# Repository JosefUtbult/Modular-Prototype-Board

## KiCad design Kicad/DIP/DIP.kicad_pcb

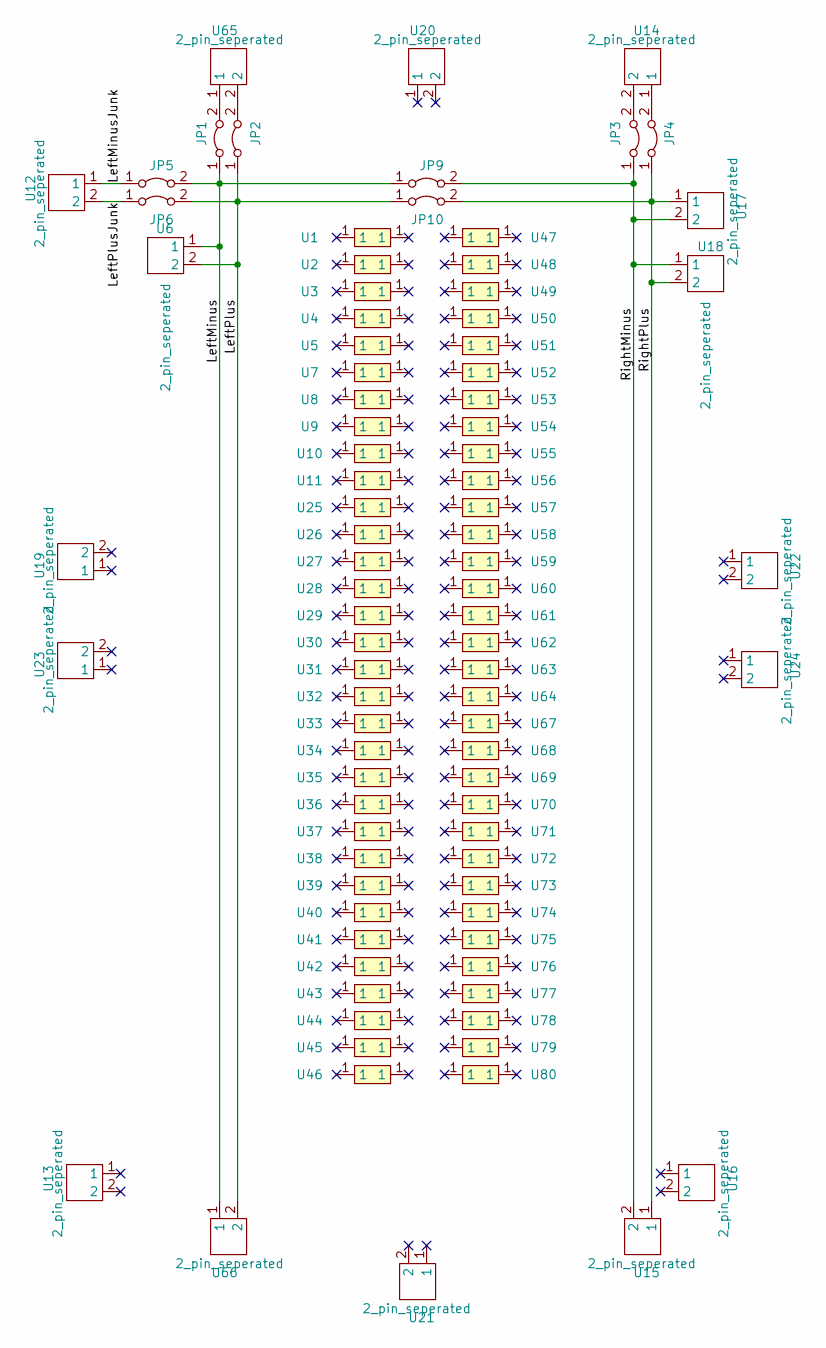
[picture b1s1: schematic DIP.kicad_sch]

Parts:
JP1, JP2, JP3, JP4, JP5, JP6, JP9, JP10: Jumper_2_Bridged; SolderJumper-2_P1.3mm_Bridged_RoundedPad1.0x1.5mm
U1, U2, U3, U47, U48: 1_row_connected; 8_pin_connection
U4, U5, U7, U8, U9, U10, U11, U25, U26, U27, U28, U29, U30, U31, U32, U33, U34, U35, U36, U37, U38, U39, U40, U41, U42, U43, U44, U45, U46, U49, U50, U51, U52, U53, U54, U55, U56, U57, U58, U59, U60, U61, U62, U63, U64, U67, U68, U69, U70, U71, U72, U73, U74, U75, U76, U77, U78, U79, U80: 1_row_connected; 9_pin_connection
U6: 2_pin_seperated; 30x2_pin_connected
U12, U13, U14, U15, U16, U17, U19, U20, U21, U22, U23, U24, U65, U66: 2_pin_seperated
U18: 2_pin_seperated; 31x2_pin_connected

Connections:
/LeftMinus: JP1.1 (A), JP5.2 (B), JP9.1 (A), U6.1, U66.1
/LeftMinusJunk: JP5.1 (A), U12.1
/LeftPlus: JP2.1 (A), JP6.2 (B), JP10.1 (A), U6.2, U66.2
/LeftPlusJunk: JP6.1 (A), U12.2
/RightMinus: JP3.1 (A), JP9.2 (B), U15.2, U17.2, U18.1
/RightPlus: JP4.1 (A), JP10.2 (B), U15.1, U17.1, U18.2
unnamed: JP1.2 (B), U65.1
unnamed: JP2.2 (B), U65.2
unnamed: JP3.2 (B), U14.2
unnamed: JP4.2 (B), U14.1

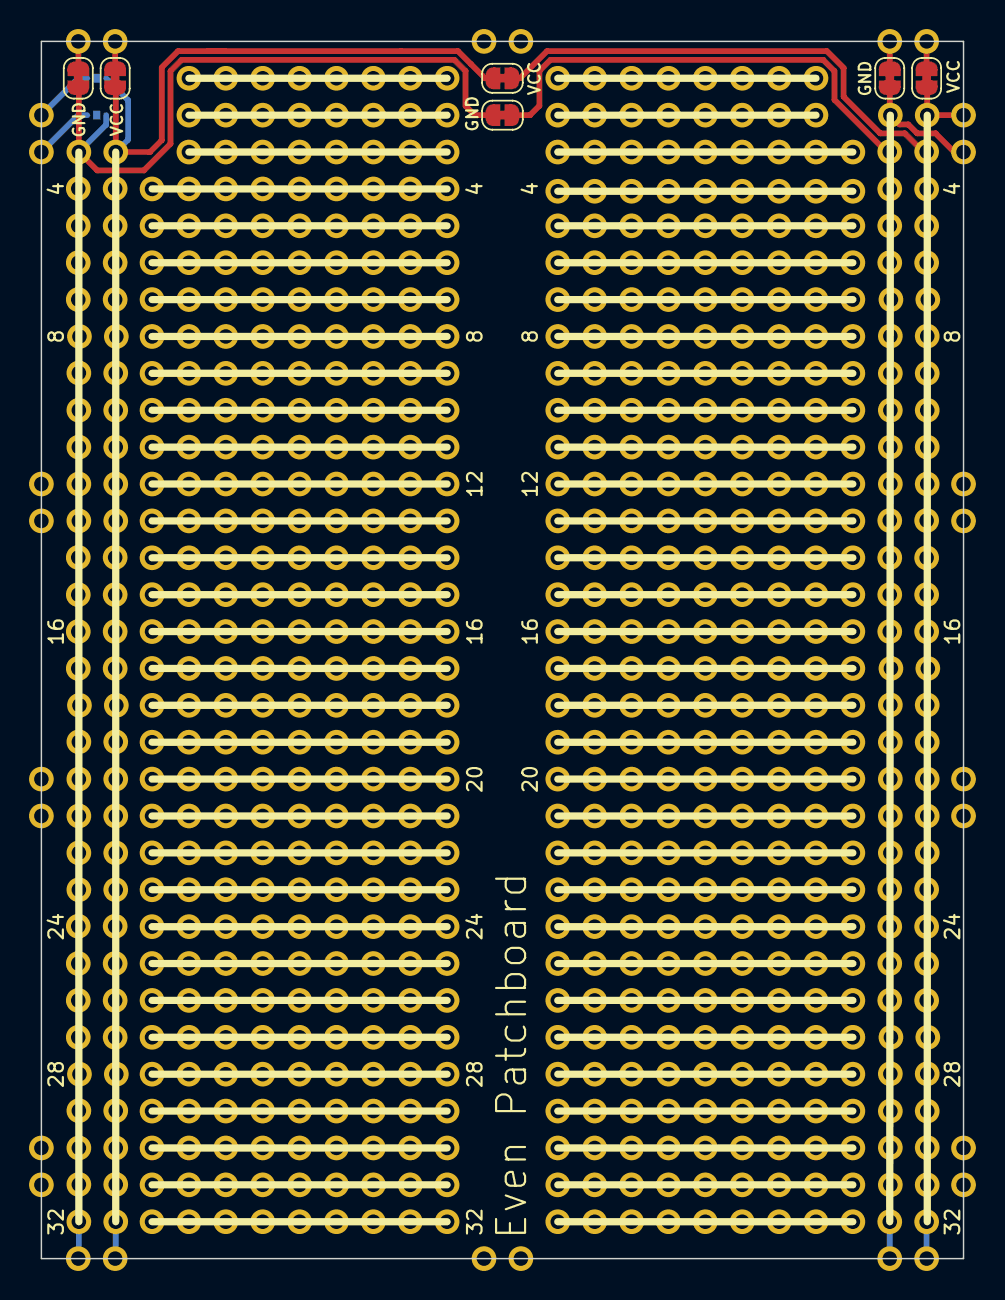
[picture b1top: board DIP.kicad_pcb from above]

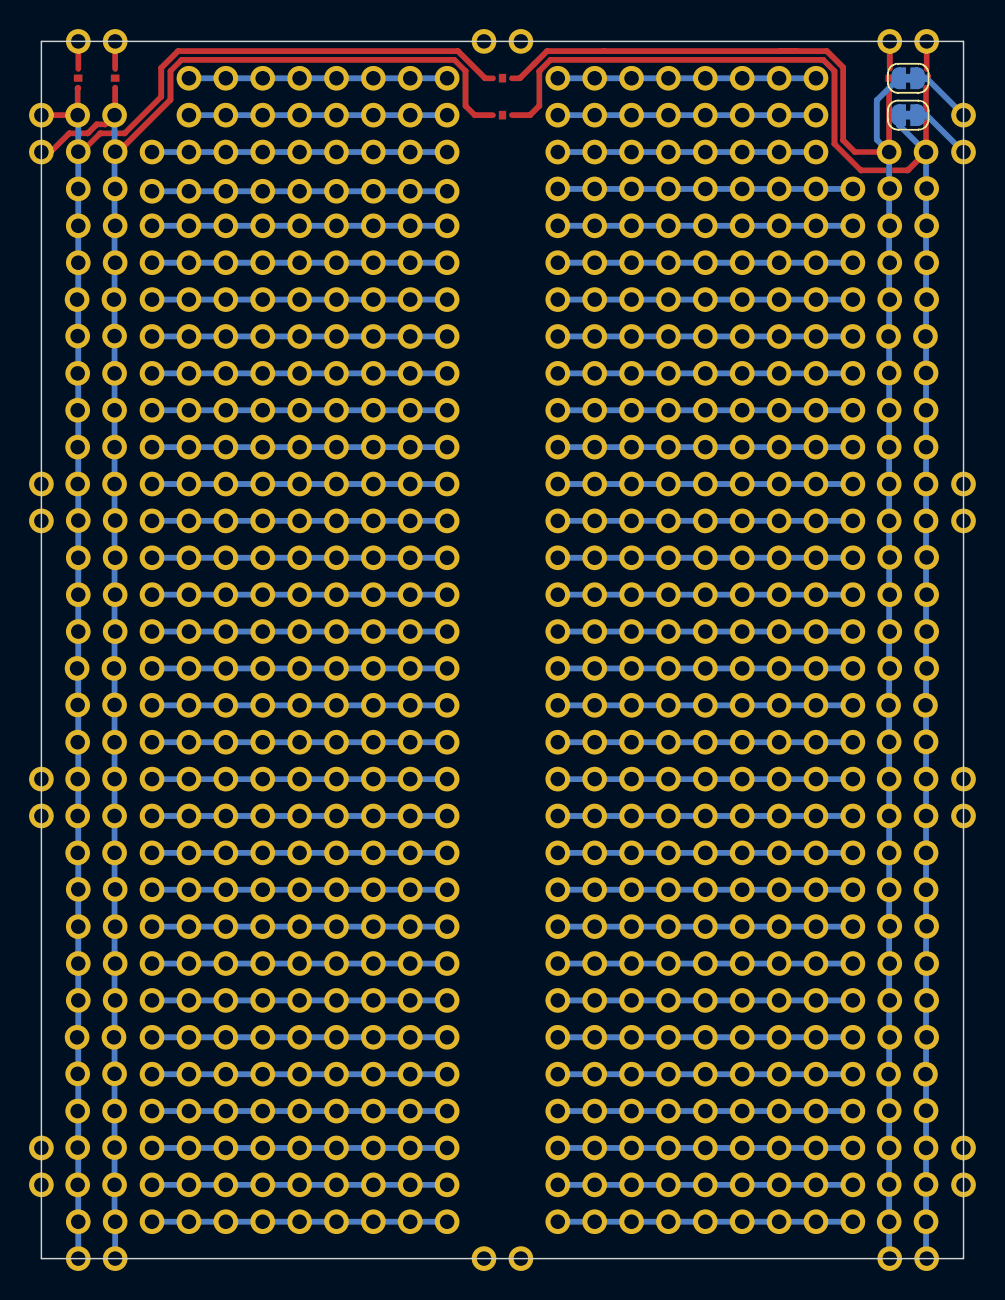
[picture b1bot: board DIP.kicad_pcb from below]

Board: 2 copper layers, 63.5 x 83.8 mm, 88 parts (2 on the bottom side), 10 nets.

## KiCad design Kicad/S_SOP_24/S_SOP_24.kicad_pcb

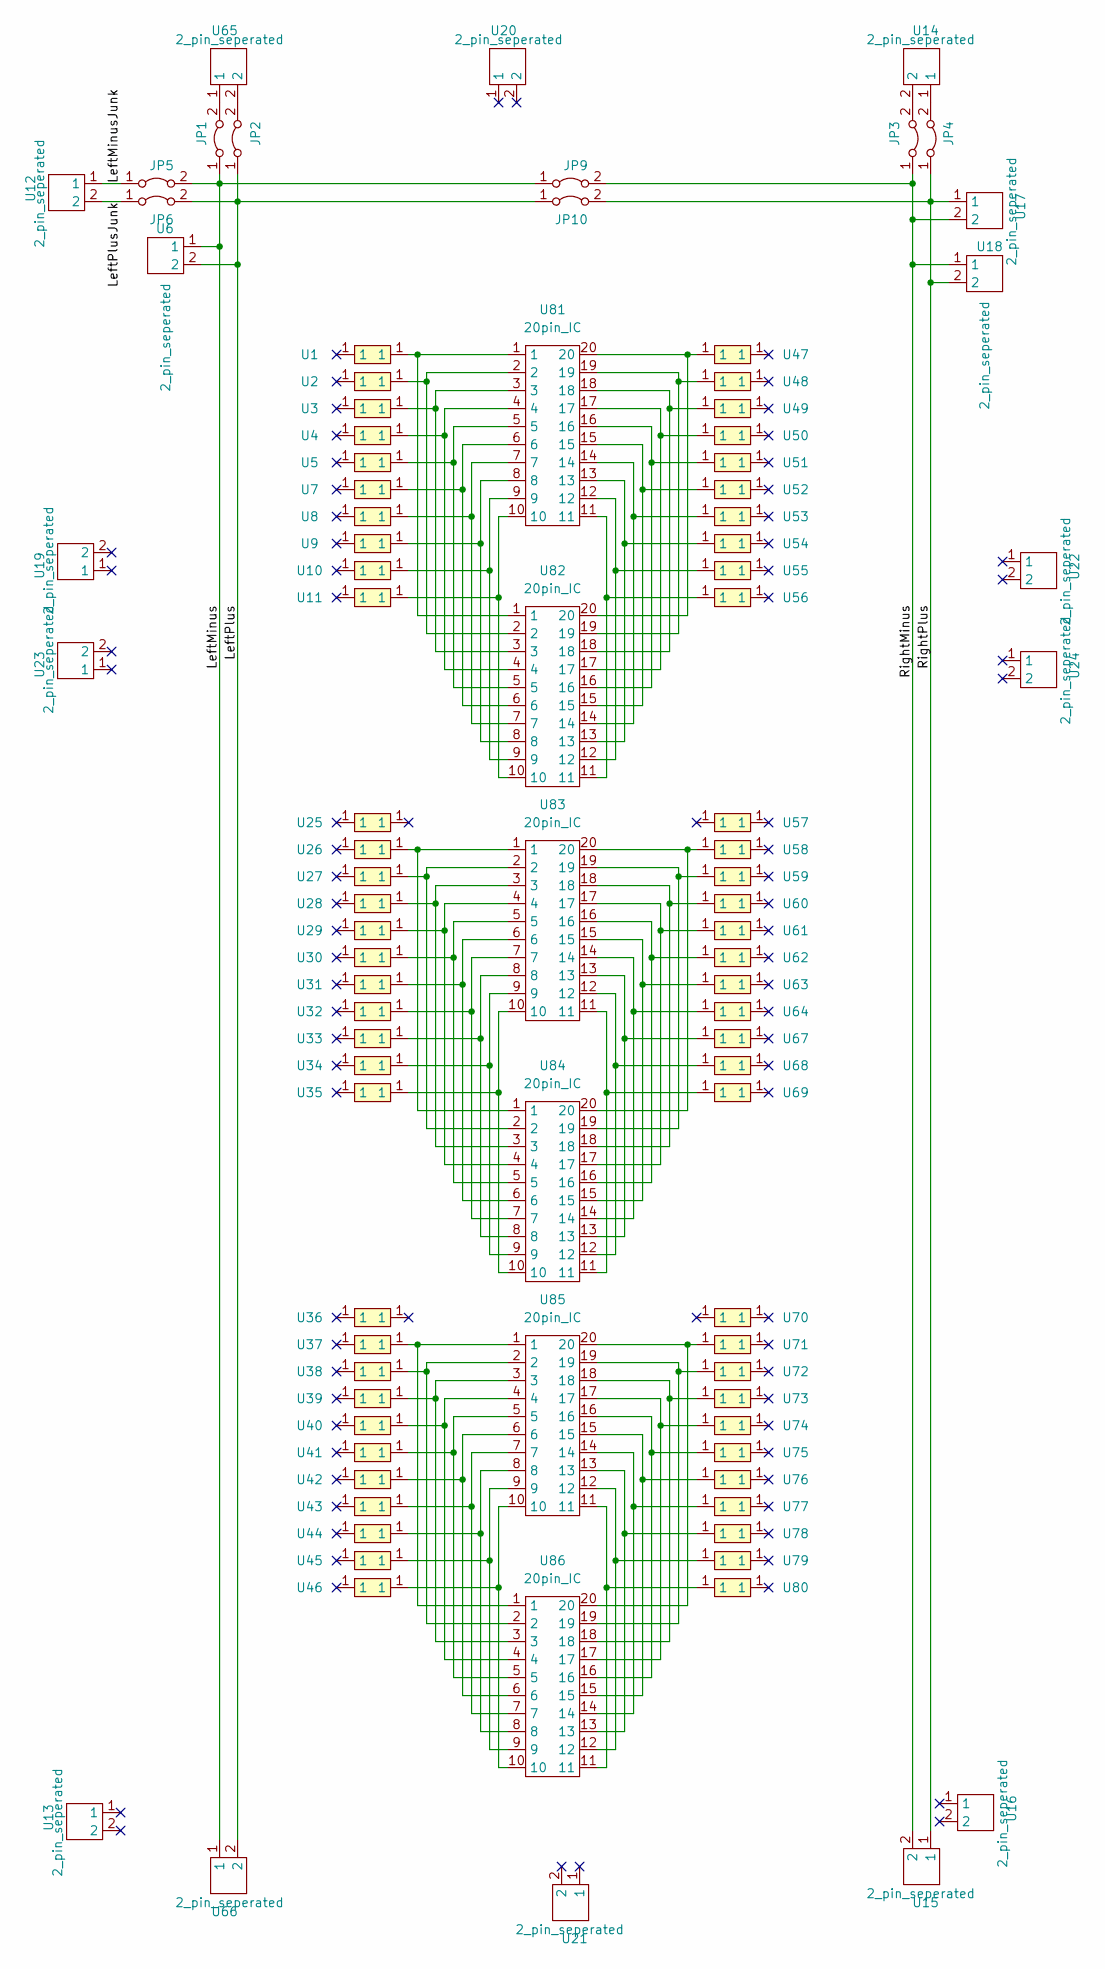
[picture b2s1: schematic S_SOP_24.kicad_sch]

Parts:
JP1, JP2, JP3, JP4, JP5, JP6, JP9, JP10: Jumper_2_Bridged; SolderJumper-2_P1.3mm_Bridged_RoundedPad1.0x1.5mm
U1, U2, U3, U47, U48: 1_row_connected; 5_pin_connection
U4, U5, U7, U8, U9, U10, U11, U25, U26, U27, U28, U29, U30, U31, U32, U33, U34, U35, U36, U37, U38, U39, U40, U41, U42, U43, U44, U45, U46, U49, U50, U51, U52, U53, U54, U55, U56, U57, U58, U59, U60, U61, U62, U63, U64, U67, U68, U69, U70, U71, U72, U73, U74, U75, U76, U77, U78, U79, U80: 1_row_connected; 6_pin_connection
U6: 2_pin_seperated; 30x2_pin_connected
U12, U13, U14, U15, U16, U17, U19, U20, U21, U22, U23, U24, U65, U66: 2_pin_seperated
U18: 2_pin_seperated; 31x2_pin_connected
U81, U83, U85: 20pin_IC; SSOP-20
U82, U84, U86: 20pin_IC; SOP-20

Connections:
/LeftMinus: JP1.1 (A), JP5.2 (B), JP9.1 (A), U6.1, U66.1
/LeftMinusJunk: JP5.1 (A), U12.1
/LeftPlus: JP2.1 (A), JP6.2 (B), JP10.1 (A), U6.2, U66.2
/LeftPlusJunk: JP6.1 (A), U12.2
/RightMinus: JP3.1 (A), JP9.2 (B), U15.2, U17.2, U18.1
/RightPlus: JP4.1 (A), JP10.2 (B), U15.1, U17.1, U18.2
unnamed: JP1.2 (B), U65.1
unnamed: JP2.2 (B), U65.2
unnamed: JP3.2 (B), U14.2
unnamed: JP4.2 (B), U14.1
unnamed: U1.1, U81.1, U82.1
unnamed: U2.1, U81.2, U82.2
unnamed: U3.1, U81.3, U82.3
unnamed: U4.1, U81.4, U82.4
unnamed: U5.1, U81.5, U82.5
unnamed: U7.1, U81.6, U82.6
unnamed: U8.1, U81.7, U82.7
unnamed: U9.1, U81.8, U82.8
unnamed: U10.1, U81.9, U82.9
unnamed: U11.1, U81.10, U82.10
unnamed: U26.1, U83.1, U84.1
unnamed: U27.1, U83.2, U84.2
unnamed: U28.1, U83.3, U84.3
unnamed: U29.1, U83.4, U84.4
unnamed: U30.1, U83.5, U84.5
unnamed: U31.1, U83.6, U84.6
unnamed: U32.1, U83.7, U84.7
unnamed: U33.1, U83.8, U84.8
unnamed: U34.1, U83.9, U84.9
unnamed: U35.1, U83.10, U84.10
unnamed: U37.1, U85.1, U86.1
unnamed: U38.1, U85.2, U86.2
unnamed: U39.1, U85.3, U86.3
unnamed: U40.1, U85.4, U86.4
unnamed: U41.1, U85.5, U86.5
unnamed: U42.1, U85.6, U86.6
unnamed: U43.1, U85.7, U86.7
unnamed: U44.1, U85.8, U86.8
unnamed: U45.1, U85.9, U86.9
unnamed: U46.1, U85.10, U86.10
unnamed: U47.1, U81.20, U82.20
unnamed: U48.1, U81.19, U82.19
unnamed: U49.1, U81.18, U82.18
unnamed: U50.1, U81.17, U82.17
unnamed: U51.1, U81.16, U82.16
unnamed: U52.1, U81.15, U82.15
unnamed: U53.1, U81.14, U82.14
unnamed: U54.1, U81.13, U82.13
unnamed: U55.1, U81.12, U82.12
unnamed: U56.1, U81.11, U82.11
unnamed: U58.1, U83.20, U84.20
unnamed: U59.1, U83.19, U84.19
unnamed: U60.1, U83.18, U84.18
unnamed: U61.1, U83.17, U84.17
unnamed: U62.1, U83.16, U84.16
unnamed: U63.1, U83.15, U84.15
unnamed: U64.1, U83.14, U84.14
unnamed: U67.1, U83.13, U84.13
unnamed: U68.1, U83.12, U84.12
unnamed: U69.1, U83.11, U84.11
unnamed: U71.1, U85.20, U86.20
unnamed: U72.1, U85.19, U86.19
unnamed: U73.1, U85.18, U86.18
unnamed: U74.1, U85.17, U86.17
unnamed: U75.1, U85.16, U86.16
unnamed: U76.1, U85.15, U86.15
unnamed: U77.1, U85.14, U86.14
unnamed: U78.1, U85.13, U86.13
unnamed: U80.1, U85.11, U86.11
unnamed: U79.1, U85.12, U86.12

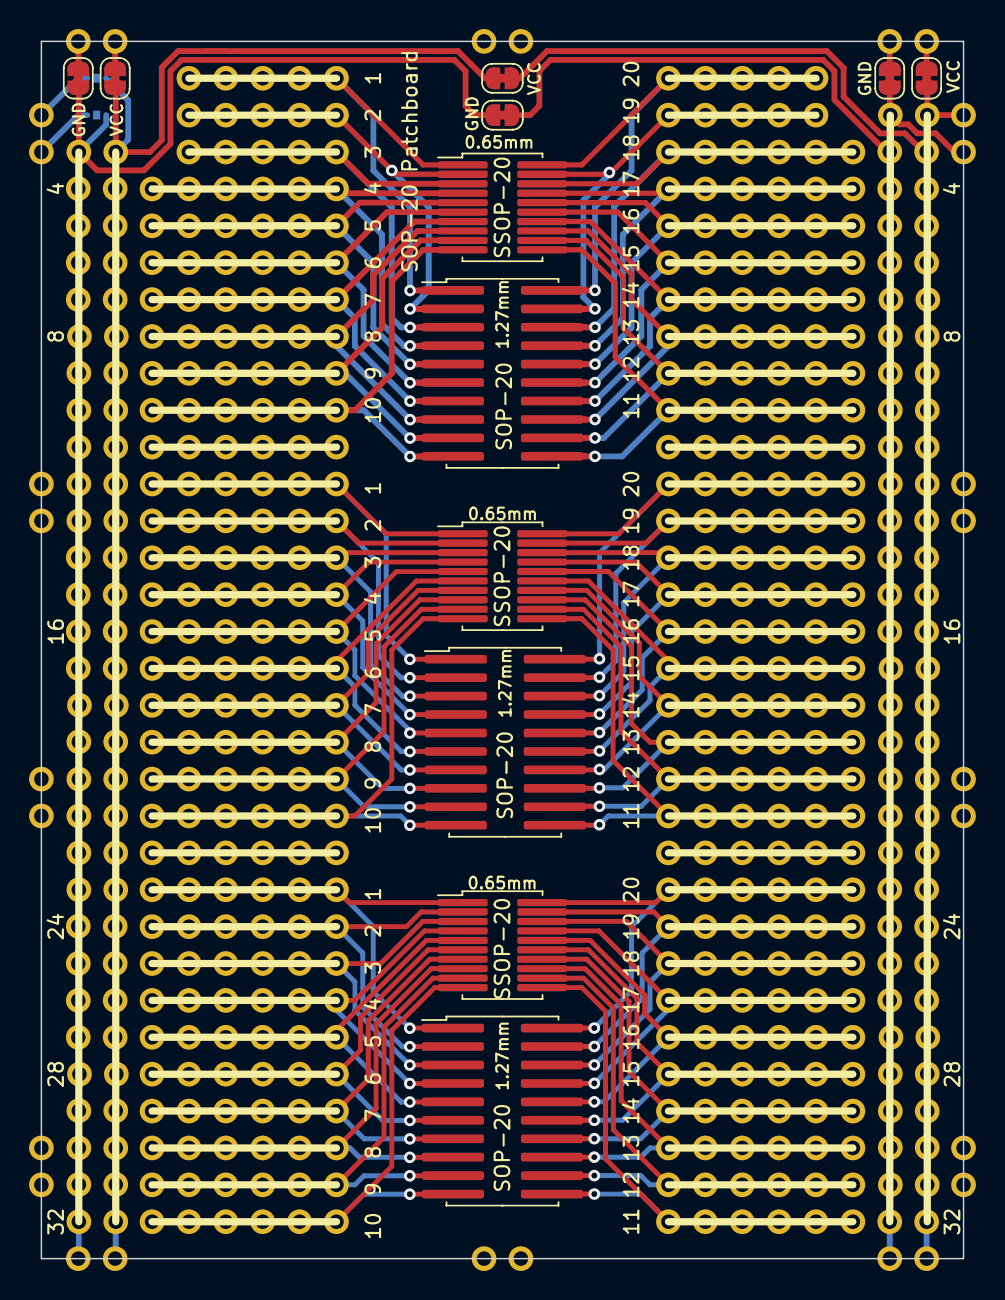
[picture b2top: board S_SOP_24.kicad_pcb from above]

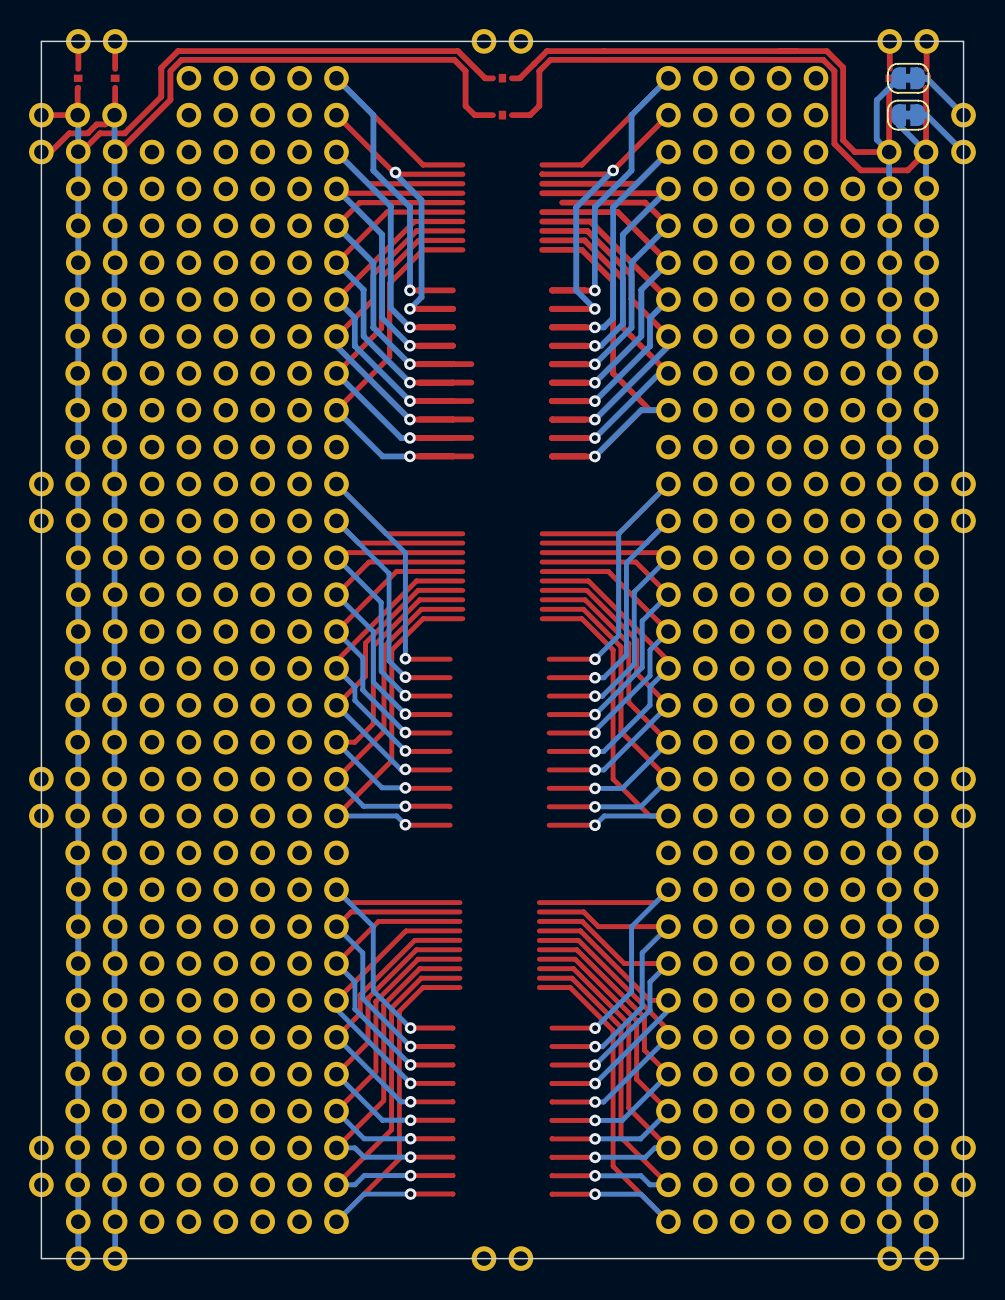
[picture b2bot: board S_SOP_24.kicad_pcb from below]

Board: 2 copper layers, 63.5 x 83.8 mm, 94 parts (2 on the bottom side), 70 nets.

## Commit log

2023-01-25 Init
